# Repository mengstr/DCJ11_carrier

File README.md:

# DCJ11_carrier

To protect the sensitive pins on the DCJ11 CPU, I designed a small carrier board to keep it safe.

I added a few extras to the board, like reverse polarity protection—just a simple reverse diode that shorts the power if applied incorrectly. (I know it really should have been a proper P-MOS instead, but hey, it’s better than nothing.) 

I also included pull-ups and pull-downs on the inputs since many of them won’t be in use for simple applications. This keeps them stable at the carrier level, so there’s no need to add jumpers externally. After the images here is a table with the pinout indicating which pins that have the pulls on them.

There are also two extra capacitor footprints on the top side of the carrier if needed, though the DCJ11 itself seems to have plenty of local capacitance. Just for fun, I added footprints for a few LEDs and resistors, hoping that the ceramic package of the DCJ11 would let some light through and create a cool glowing effect—but no joy. The ceramic is completely opaque.

The PCB is designed to use turned IC socket contacts. The row with smaller holes is for the DCJ11 itself, lifting it up a few millimeters above the PCB. The larger holes allow the contacts to drop down fully to their flanges, making them protrude as much as possible below the board so the carrier can later be inserted into the user motherboard.

### DCJ11 plugged into the PCB and the LEDs turned on.

### Front- and backside of the PCB

### How the turned pin headers are mounted

## Pinout of the DCJ11

| Pin# | Direction | Pull   | Name    | Description          |
| --- | --- | -- | ------- | -------------------- |
| 1   | in  | pu | nTEST1  | Test input           |
| 2   | out |    | AIO 0   | Address I/O 0        |
| 3   | out |    | AIO 1   | Address I/O 1        |
| 4   | out |    | AIO 2   | Address I/O 2        |
| 5   | out |    | AIO 3   | Address I/O 3        |
| 6   | in  | pu | nPWRF   | Power fail           |
| 7   | in  | pu | nFPE    | Floating-point error |
| 8   | in  | pu | nEVENT  | Event interrupt      |
| 9   | in  | pd | HALT    | Halt processor       |
| 10  | in  | pd | IRQ0    | Interrupt request 0  |
| 11  | in  | pd | IRQ1    | Interrupt request 1  |
| 12  | in  | pd | IRQ2    | Interrupt request 2  |
| 13  | in  | pd | IRQ3    | Interrupt request 3  |
| 14  | in  | pu | nPARITY | Parity check         |
| 15  | -   |    | GND     | Ground (0V)          |
| 16  | -   |    | VCC     | Power (5V)           |
| 17  | out |    | BS 0    | Bus strobe 0         |
| 18  | out |    | BS 1    | Bus strobe 1         |
| 19  | out |    | nMAP    | Memory map control   |
| 20  | i/o |    | nABORT  | Abort cycle          |
| 21  | out |    | DAL21   | Data/address line 21 |
| 22  | out |    | DAL20   | Data/address line 20 |
| 23  | out |    | DAL19   | Data/address line 19 |
| 24  | out |    | DAL18   | Data/address line 18 |
| 25  | out |    | DAL17   | Data/address line 17 |
| 26  | out |    | DAL16   | Data/address line 16 |
| 27  | in  | pu | nDMR    | DMA request          |
| 28  | in  | pu | nMISS   | Cache miss           |
| 29  | out |    | nPRDC   | Predict control      |
| 30  | -   |    | N.C.    | Unused pin           |
| 31  | in  | pu | nTEST2  | Test output          |
| 32  | in  | pu | nCONT   | Continue signal      |
| 33  | in  | pu | nINIT   | Initialize           |
| 34  | out |    | CLK2    | Clock 2              |
| 35  | i/o |    | CLK     | Clock                |
| 36  | in  |    | XTALHI  | Crystal input        |
| 37  | out |    | XTALLO  | Crystal output       |
| 38  | out |    | nSCTL   | Strobe control       |
| 39  | out |    | nSTRB   | Strobe signal        |
| 40  | out |    | nALE    | Address latch enable |
| 41  | out |    | nBUFCTL | Buffer control       |
| 42  | in  | pu | DV      | Device vector        |
| 43  | i/o |    | DAL5    | Data/address line 5  |
| 44  | i/o |    | DAL4    | Data/address line 4  |
| 45  | -   |    | GND     | Ground (0V)          |
| 46  | -   |    | VCC     | Power (5V)           |
| 47  | i/o |    | DAL3    | Data/address line 3  |
| 48  | i/o |    | DAL2    | Data/address line 2  |
| 49  | i/o |    | DAL1    | Data/address line 1  |
| 50  | i/o |    | DAL15   | Data/address line 15 |
| 51  | i/o |    | DAL14   | Data/address line 14 |
| 52  | i/o |    | DAL13   | Data/address line 13 |
| 53  | i/o |    | DAL12   | Data/address line 12 |
| 54  | i/o |    | DAL11   | Data/address line 11 |
| 55  | i/o |    | DAL10   | Data/address line 10 |
| 56  | i/o |    | DAL9    | Data/address line 9  |
| 57  | i/o |    | DAL0    | Data/address line 0  |
| 58  | i/o |    | DAL8    | Data/address line 8  |
| 59  | i/o |    | DAL7    | Data/address line 7  |
| 60  | i/o |    | DAL6    | Data/address line 6  |

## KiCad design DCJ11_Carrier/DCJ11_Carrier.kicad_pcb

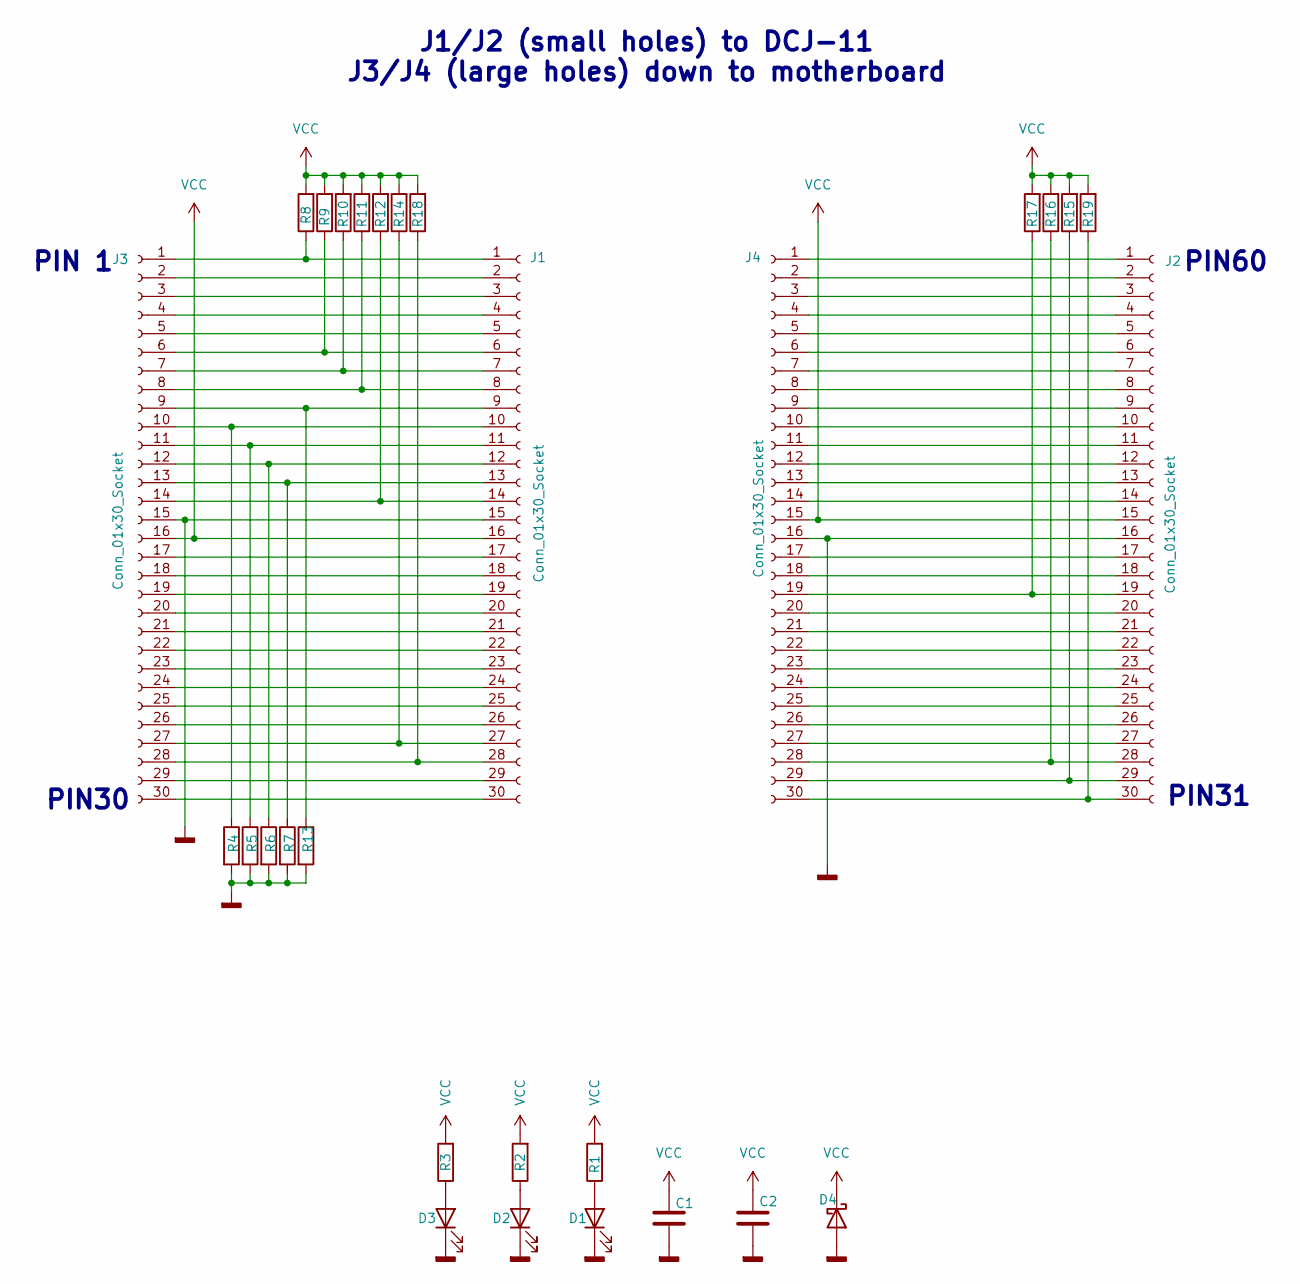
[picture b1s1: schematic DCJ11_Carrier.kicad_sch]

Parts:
C1, C2: C; C_0805_2012Metric_Pad1.18x1.45mm_HandSolder
D1, D2, D3: LED; LED_0805_2012Metric_Pad1.15x1.40mm_HandSolder
D4: B220; D_SMB
J1, J2, J3, J4: Conn_01x30_Socket; PinSocket_1x30_P2.54mm_Vertical
R1, R2, R3, R4, R5, R6, R7, R8, R9, R10, R11, R12, R13, R14, R15, R16, R17, R18, R19: R; R_0805_2012Metric_Pad1.20x1.40mm_HandSolder

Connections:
GND: C1.2, C2.2, D1.1 (K), D2.1 (K), D3.1 (K), D4.2 (A), J1.15, J2.16, J3.15, J4.16, R4.2, R5.2, R6.2, R7.2, R13.2
unnamed: D1.2 (A), R1.1
unnamed: D2.2 (A), R2.1
unnamed: D3.2 (A), R3.1
unnamed: J1.1, J3.1, R8.1
unnamed: J1.2, J3.2
unnamed: J1.3, J3.3
unnamed: J1.4, J3.4
unnamed: J1.5, J3.5
unnamed: J1.6, J3.6, R9.1
unnamed: J1.7, J3.7, R10.1
unnamed: J1.8, J3.8, R11.1
unnamed: J1.9, J3.9, R13.1
unnamed: J1.10, J3.10, R4.1
unnamed: J1.11, J3.11, R5.1
unnamed: J1.12, J3.12, R6.1
unnamed: J1.13, J3.13, R7.1
unnamed: J1.14, J3.14, R12.1
unnamed: J1.17, J3.17
unnamed: J1.18, J3.18
unnamed: J1.19, J3.19
unnamed: J1.20, J3.20
unnamed: J1.21, J3.21
unnamed: J1.22, J3.22
unnamed: J1.23, J3.23
unnamed: J1.24, J3.24
unnamed: J1.25, J3.25
unnamed: J1.26, J3.26
unnamed: J1.27, J3.27, R14.1
unnamed: J1.28, J3.28, R18.1
unnamed: J1.29, J3.29
unnamed: J1.30, J3.30
unnamed: J2.1, J4.1
unnamed: J2.2, J4.2
unnamed: J2.3, J4.3
unnamed: J2.4, J4.4
unnamed: J2.5, J4.5
unnamed: J2.6, J4.6
unnamed: J2.7, J4.7
unnamed: J2.8, J4.8
unnamed: J2.9, J4.9
unnamed: J2.10, J4.10
unnamed: J2.11, J4.11
unnamed: J2.12, J4.12
unnamed: J2.13, J4.13
unnamed: J2.14, J4.14
unnamed: J2.17, J4.17
unnamed: J2.18, J4.18
unnamed: J2.19, J4.19, R17.1
unnamed: J2.20, J4.20
unnamed: J2.21, J4.21
unnamed: J2.22, J4.22
unnamed: J2.23, J4.23
unnamed: J2.24, J4.24
unnamed: J2.25, J4.25
unnamed: J2.26, J4.26
unnamed: J2.27, J4.27
unnamed: J2.28, J4.28, R16.1
unnamed: J2.29, J4.29, R15.1
unnamed: J2.30, J4.30, R19.1
VCC: C1.1, C2.1, D4.1 (K), J1.16, J2.15, J3.16, J4.15, R1.2, R2.2, R3.2, R8.2, R9.2, R10.2, R11.2, R12.2, R14.2, R15.2, R16.2, R17.2, R18.2, R19.2

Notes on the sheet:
PIN31
PIN30
PIN60
J1/J2 (small holes) to DCJ-11 J3/J4 (large holes) down to motherboard
PIN 1

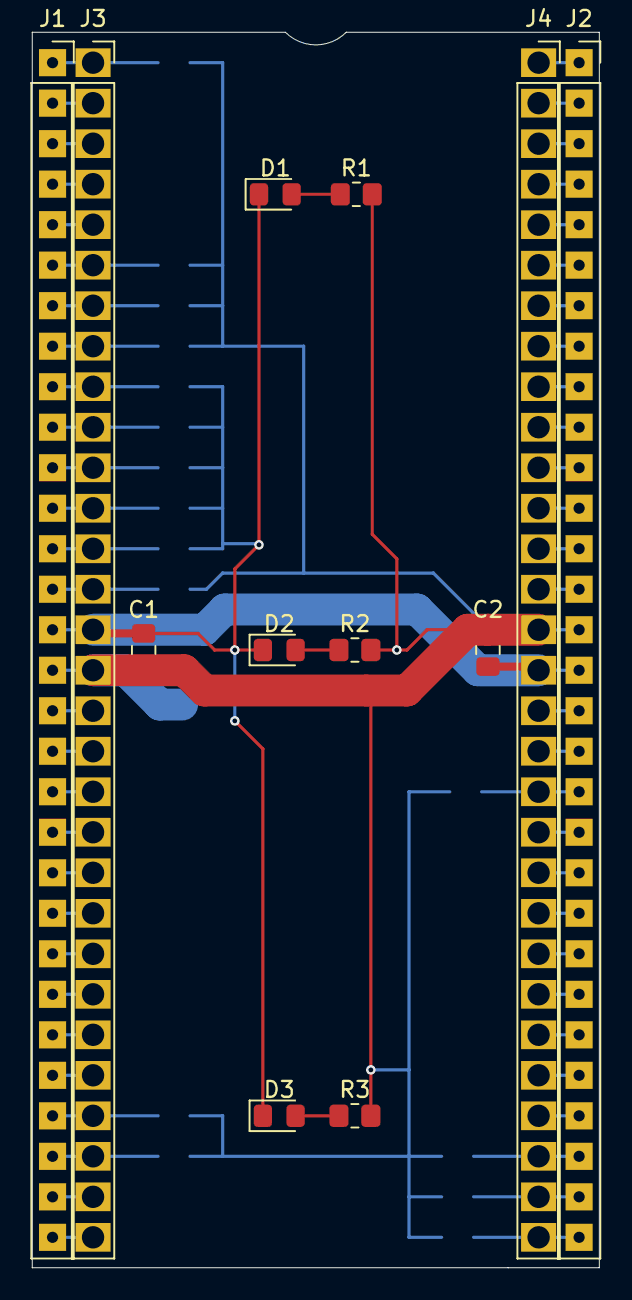
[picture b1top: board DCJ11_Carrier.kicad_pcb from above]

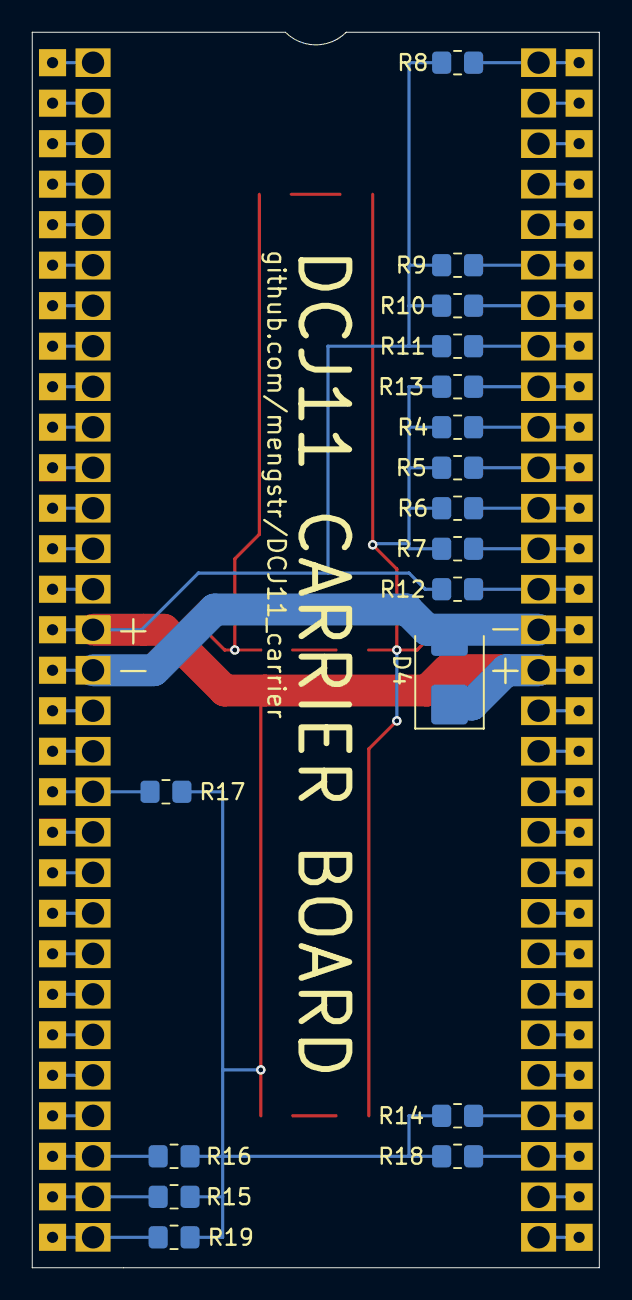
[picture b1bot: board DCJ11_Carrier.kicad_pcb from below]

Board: 2 copper layers, 35.6 x 77.5 mm, 29 parts (17 on the bottom side), 61 nets.

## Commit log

2025-02-21 Add images
2025-02-21 Add Kicad files
2025-02-21 Add schematic as PDF
